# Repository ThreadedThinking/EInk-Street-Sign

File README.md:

# E-Ink Street Sign - Econotag
SEPTA Wireless Smart City Street Sign
By: Alexander Roscoe, Drew Taylor and Colin Weir

This github repository includes eink drivers for a Redwire Econotag.  This project was for a demo during the Bits-N-Bytes at the IETF conference in Toronto, Canada.  It demonstrates the use of low-power wireless communication in an urban environment.  It uses 6lowPAN and CoAP to communicate transit information from a municipal transit location API.

## Bill of Materials

  * E-ink display - LB060S01
  * Wireless Radio/MCU - Econotag - http://www.redwirellc.com/collections/frontpage/products/econotag-ii
  * E-ink Power Supply EVM - Texas Instruments TPS65185 - http://www.ti.com/tool/tps65185evm
  * Ribbon Connector - Hirose FH26-39S-0.3SHW
  * PCB - Just upload the PCB design file to oshpark.com, you should have it back in 2 weeks

#Hardware
An electrophoretic display was chosen as it can hold an image without a power and it requires very little energy to update. The screen is based on an LB060S01-RD02.  It is powered from a Texas Instruments TPS65185 power supply,  it was only $10 for a development board next-day shipped.  It provided two high efficiency DC/DC boost converters that generate ±16-V rails which are then boosted to 22 V and –20 V. It also has two tracking LDOs that create the ±15-V source driver supplies.  I didn't have to design any of these which made this project plug-N-play.

The radio uses the erbium client firmware from the Contiki OS.  This reaches out to a CoAP server to retrieve transit information. We used the econotag from Redwire as it had the most pins available to drive the screen.  The econotag has the ability to fall asleep in a lower power mode and wake up to update the display.  Because the screen and radio require very little energy, energy harvesting would be an ideal power source for perpetual operation.  The one limitition with the econotag was the flash size.  High quality fonts take up a lot of space.

The sign connects through an IPv6 internet connection based around a Raspberry Pi running 6lbr.  This border gateway passes CoAP requests from the sign to a CoAP server that proxied the requests to SEPTA's transit API.

# Credits and Links
Petteri Aimonen wrote a very good writeup on how to drive the screen.
http://essentialscrap.com/eink/software.html

All based on the Contiki OS
https://github.com/contiki-os/contiki/tree/master/examples/er-rest-example  

Border Gateway http://cetic.github.io/6lbr/

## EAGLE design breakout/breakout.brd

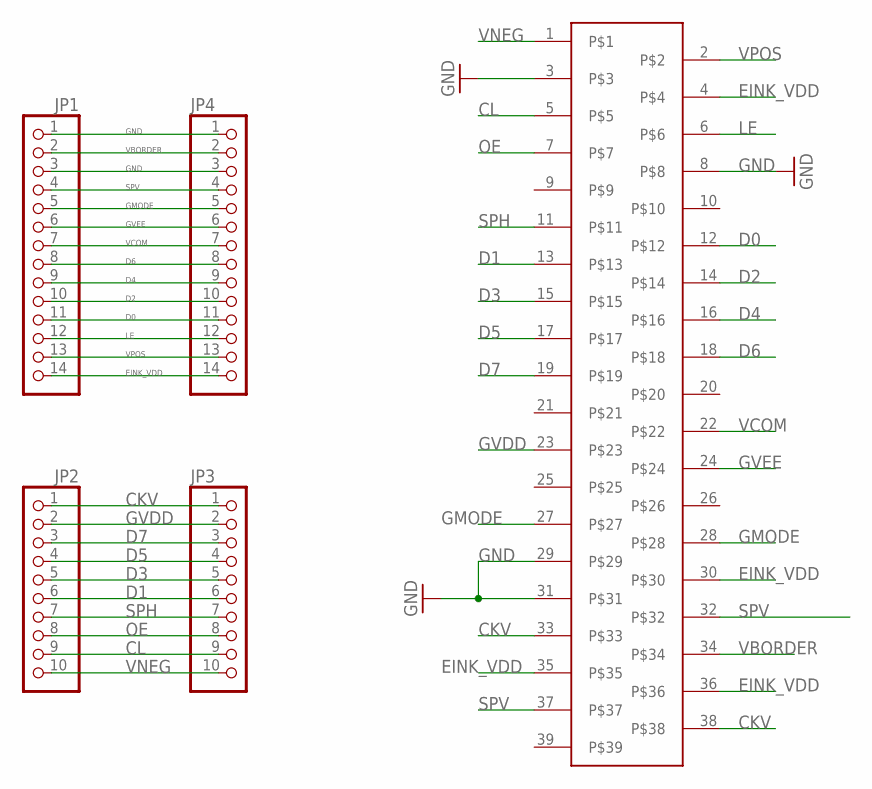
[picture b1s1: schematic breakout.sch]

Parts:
JP1, JP4: PINHD-1X14; 1X14
JP2, JP3: PINHD-1X10; 1X10
U$1: JCT-39

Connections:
CKV: JP2.1, JP3.1, U$1.33, U$1.38
CL: JP2.9, JP3.9, U$1.5
D0: JP1.11, JP4.11, U$1.12
D1: JP2.6, JP3.6, U$1.13
D2: JP1.10, JP4.10, U$1.14
D3: JP2.5, JP3.5, U$1.15
D4: JP1.9, JP4.9, U$1.16
D5: JP2.4, JP3.4, U$1.17
D6: JP1.8, JP4.8, U$1.18
D7: JP2.3, JP3.3, U$1.19
EINK_VDD: JP1.14, JP4.14, U$1.4, U$1.30, U$1.35, U$1.36
GMODE: JP1.5, JP4.5, U$1.27, U$1.28
GND: JP1.1, JP1.3, JP4.1, JP4.3, U$1.3, U$1.8, U$1.29, U$1.31
GVDD: JP2.2, JP3.2, U$1.23
GVEE: JP1.6, JP4.6, U$1.24
LE: JP1.12, JP4.12, U$1.6
OE: JP2.8, JP3.8, U$1.7
SPH: JP2.7, JP3.7, U$1.11
SPV: JP1.4, JP4.4, U$1.32, U$1.37
VBORDER: JP1.2, JP4.2, U$1.34
VCOM: JP1.7, JP4.7, U$1.22
VNEG: JP2.10, JP3.10, U$1.1
VPOS: JP1.13, JP4.13, U$1.2

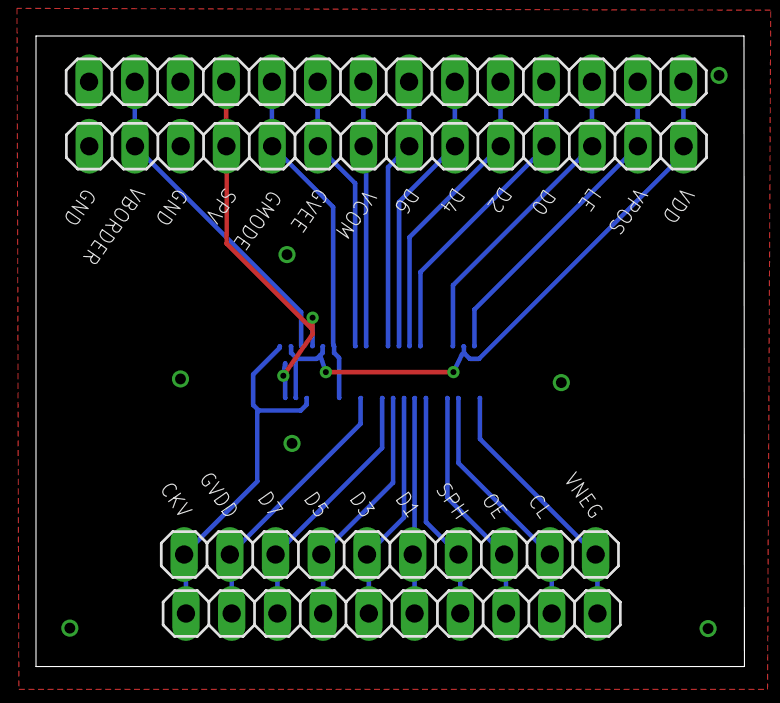
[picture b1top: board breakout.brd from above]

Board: 2 copper layers, 39.4 x 35.0 mm, 5 parts (1 on the bottom side), 23 nets.

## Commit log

2015-02-17 Images
2015-02-17 image rename
2015-02-17 image resize
2015-02-17 Source Code
2015-02-17 PCB board
2015-02-17 code removal
2015-02-17 deleted tmp files
2015-02-17 rename folder
